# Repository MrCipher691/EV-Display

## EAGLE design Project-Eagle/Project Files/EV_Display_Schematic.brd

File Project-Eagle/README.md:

# Project Files from Autodesk Eagle

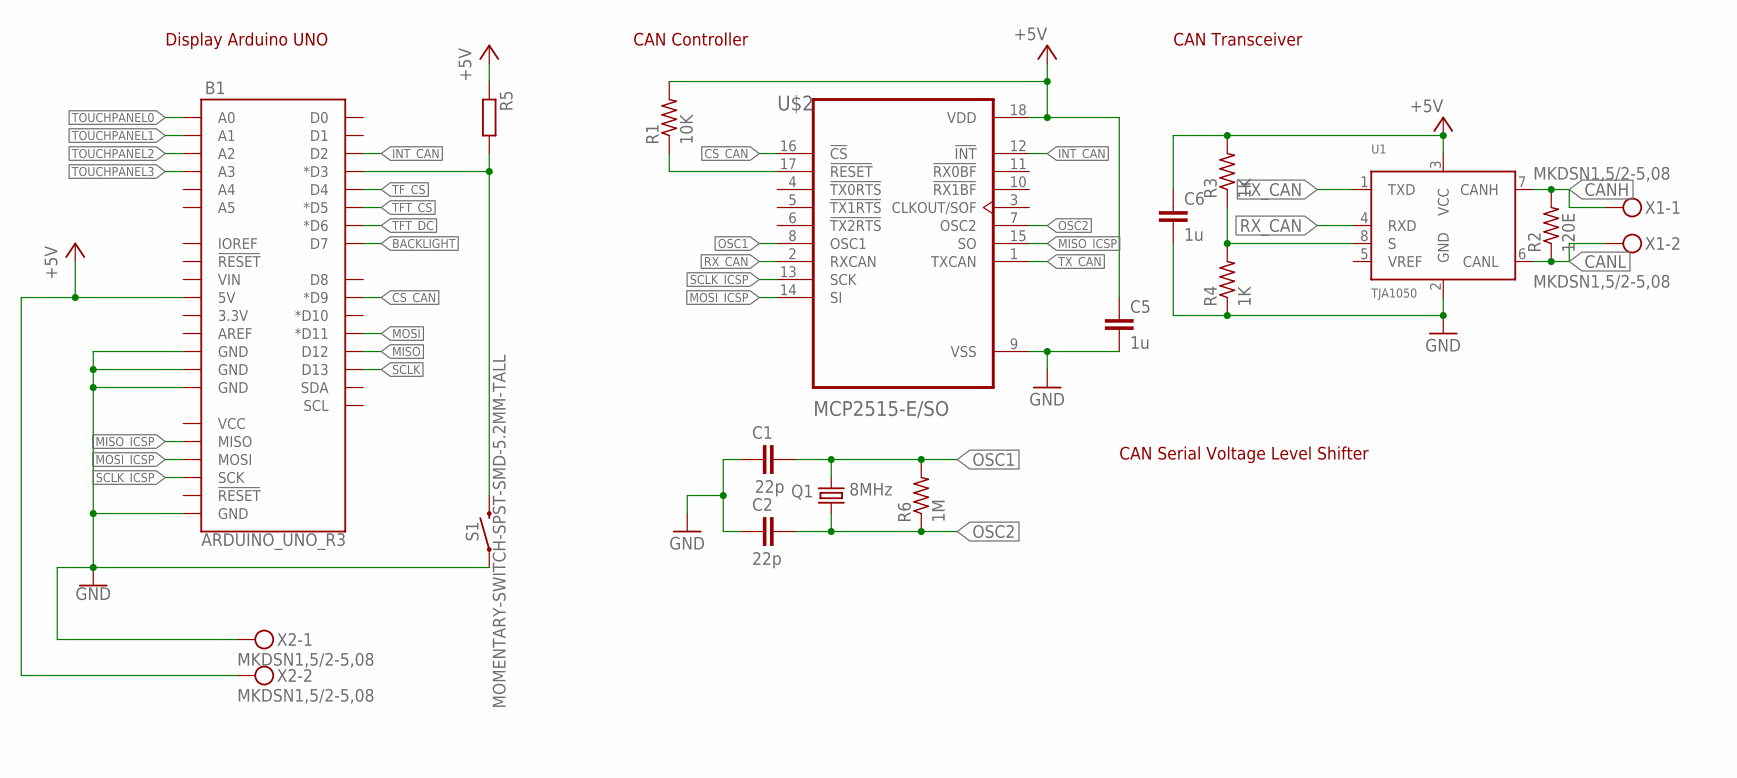
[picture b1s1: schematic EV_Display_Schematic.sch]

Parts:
B1: ARDUINO_UNO_R3; ARDUINO_R3
C1, C2: 22p; C0805
C5, C6: 1u; C0805
Q1: 8MHz; HC49/S
R1: 10K; R0805
R2: 120E; R0805
R3, R4: 1K; R0805
R5: R-EU_R0805; R0805
R6: 1M; R0805
S1: MOMENTARY-SWITCH-SPST-SMD-5.2MM-TALL; TACTILE_SWITCH_SMD_5.2MM
U1: TJA1050; SOT96-1
U$2: MCP2515-E/SO; SOIC127P1030X265-18N
X1, X2: MKDSN1,5/2-5,08

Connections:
+5V: B1.5V, C5.1, C6.1, R1.2, R3.2, R5.1, U1.3 (VCC), U$2.18 (VDD), X2.2
BACKLIGHT: B1.D7
CANH: R2.2, U1.7 (CANH), X1.1
CANL: R2.1, U1.6 (CANL), X1.2
CS_CAN: B1.D9 (*D9), U$2.16 (!CS)
GND: B1.GND@1 (GND), B1.GND@2 (GND), B1.GND@3 (GND), B1.GND@4 (GND), C1.1, C2.1, C5.2, C6.2, R4.1, S1.1, U1.2 (GND), U$2.9 (VSS), X2.1
INT_CAN: B1.D2, U$2.12 (!INT)
MISO: B1.D12
MISO_ICSP: B1.MISO, U$2.15 (SO)
MOSI: B1.D11 (*D11)
MOSI_ICSP: B1.MOSI, U$2.14 (SI)
unnamed: R1.1, U$2.17 (!RESET)
unnamed: R3.1, R4.2, U1.8 (S)
unnamed: B1.D3 (*D3), R5.2, S1.3 (2)
OSC1: C1.2, Q1.2, R6.2, U$2.8 (OSC1)
OSC2: C2.2, Q1.1, R6.1, U$2.7 (OSC2)
RX_CAN: U1.4 (RXD), U$2.2 (RXCAN)
SCLK: B1.D13
SCLK_ICSP: B1.SCK, U$2.13 (SCK)
TFT_CS: B1.D5 (*D5)
TFT_DC: B1.D6 (*D6)
TF_CS: B1.D4
TOUCHPANEL0: B1.A0
TOUCHPANEL1: B1.A1
TOUCHPANEL2: B1.A2
TOUCHPANEL3: B1.A3
TX_CAN: U1.1 (TXD), U$2.1 (TXCAN)

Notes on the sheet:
CAN Transceiver
CAN Controller
CAN Serial Voltage Level Shifter
Display Arduino UNO

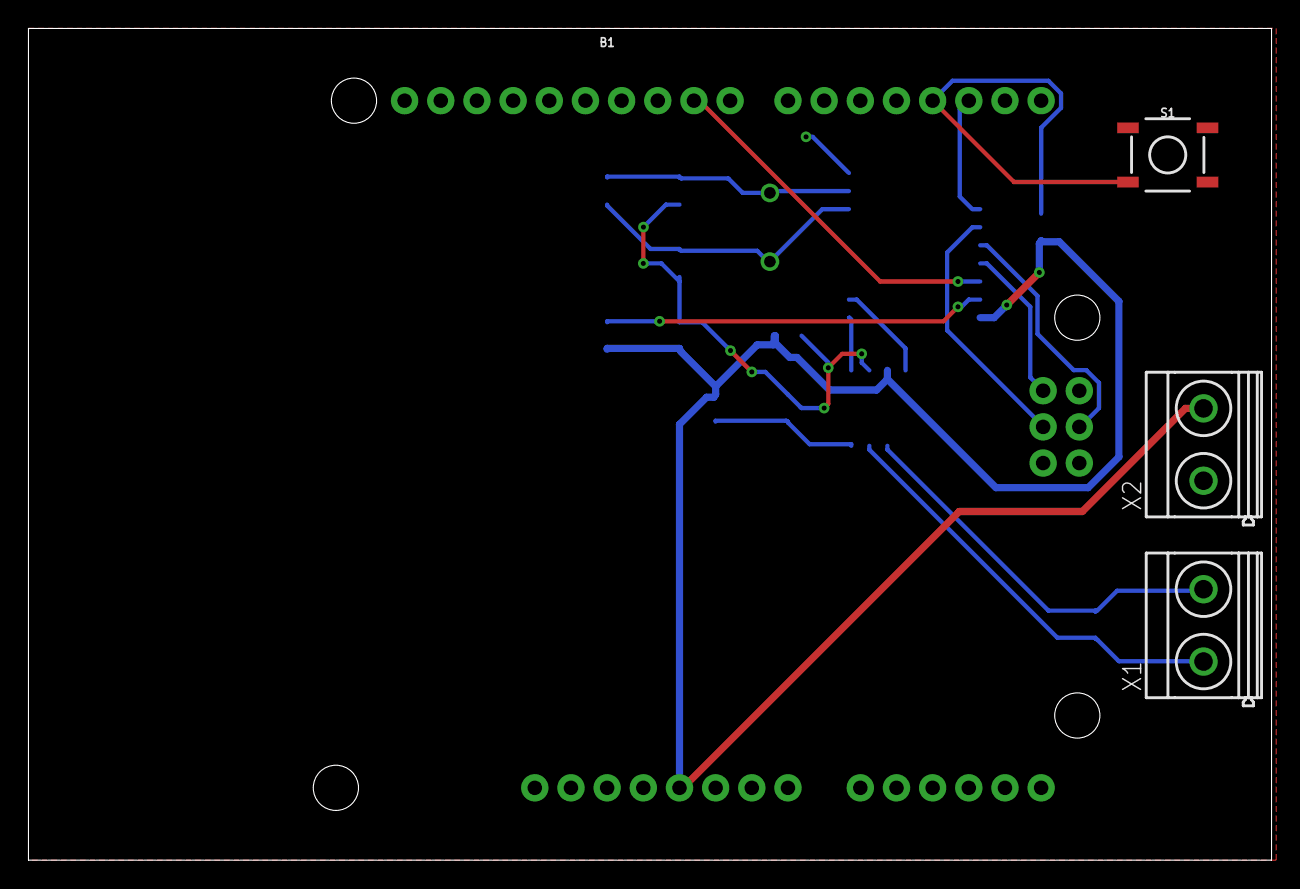
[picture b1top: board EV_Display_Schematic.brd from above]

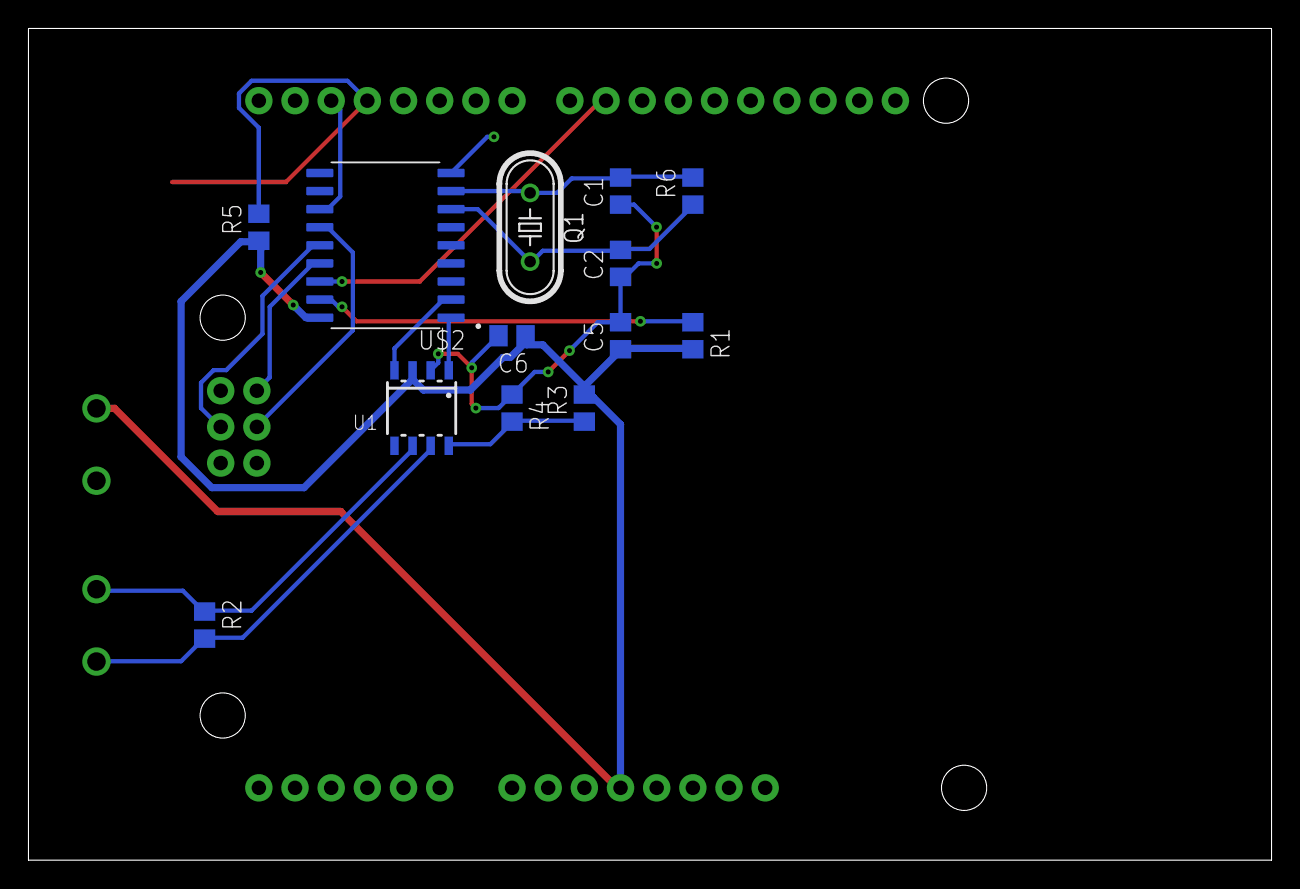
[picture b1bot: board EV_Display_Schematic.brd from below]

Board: 2 copper layers, 87.3 x 58.4 mm, 17 parts (13 on the bottom side), 16 nets.

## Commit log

2020-12-26 Required Libraries
2020-12-26 Project Files

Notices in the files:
parts and their libraries:
SparkFun-Boards: Licensing: Creative Commons ShareAlike 4.0 International - https://creativecommons.org/licenses/by-sa/4.0
